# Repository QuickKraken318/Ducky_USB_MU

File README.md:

Original project: https://github.com/Seytonic/malduino

Not tested IRL yet

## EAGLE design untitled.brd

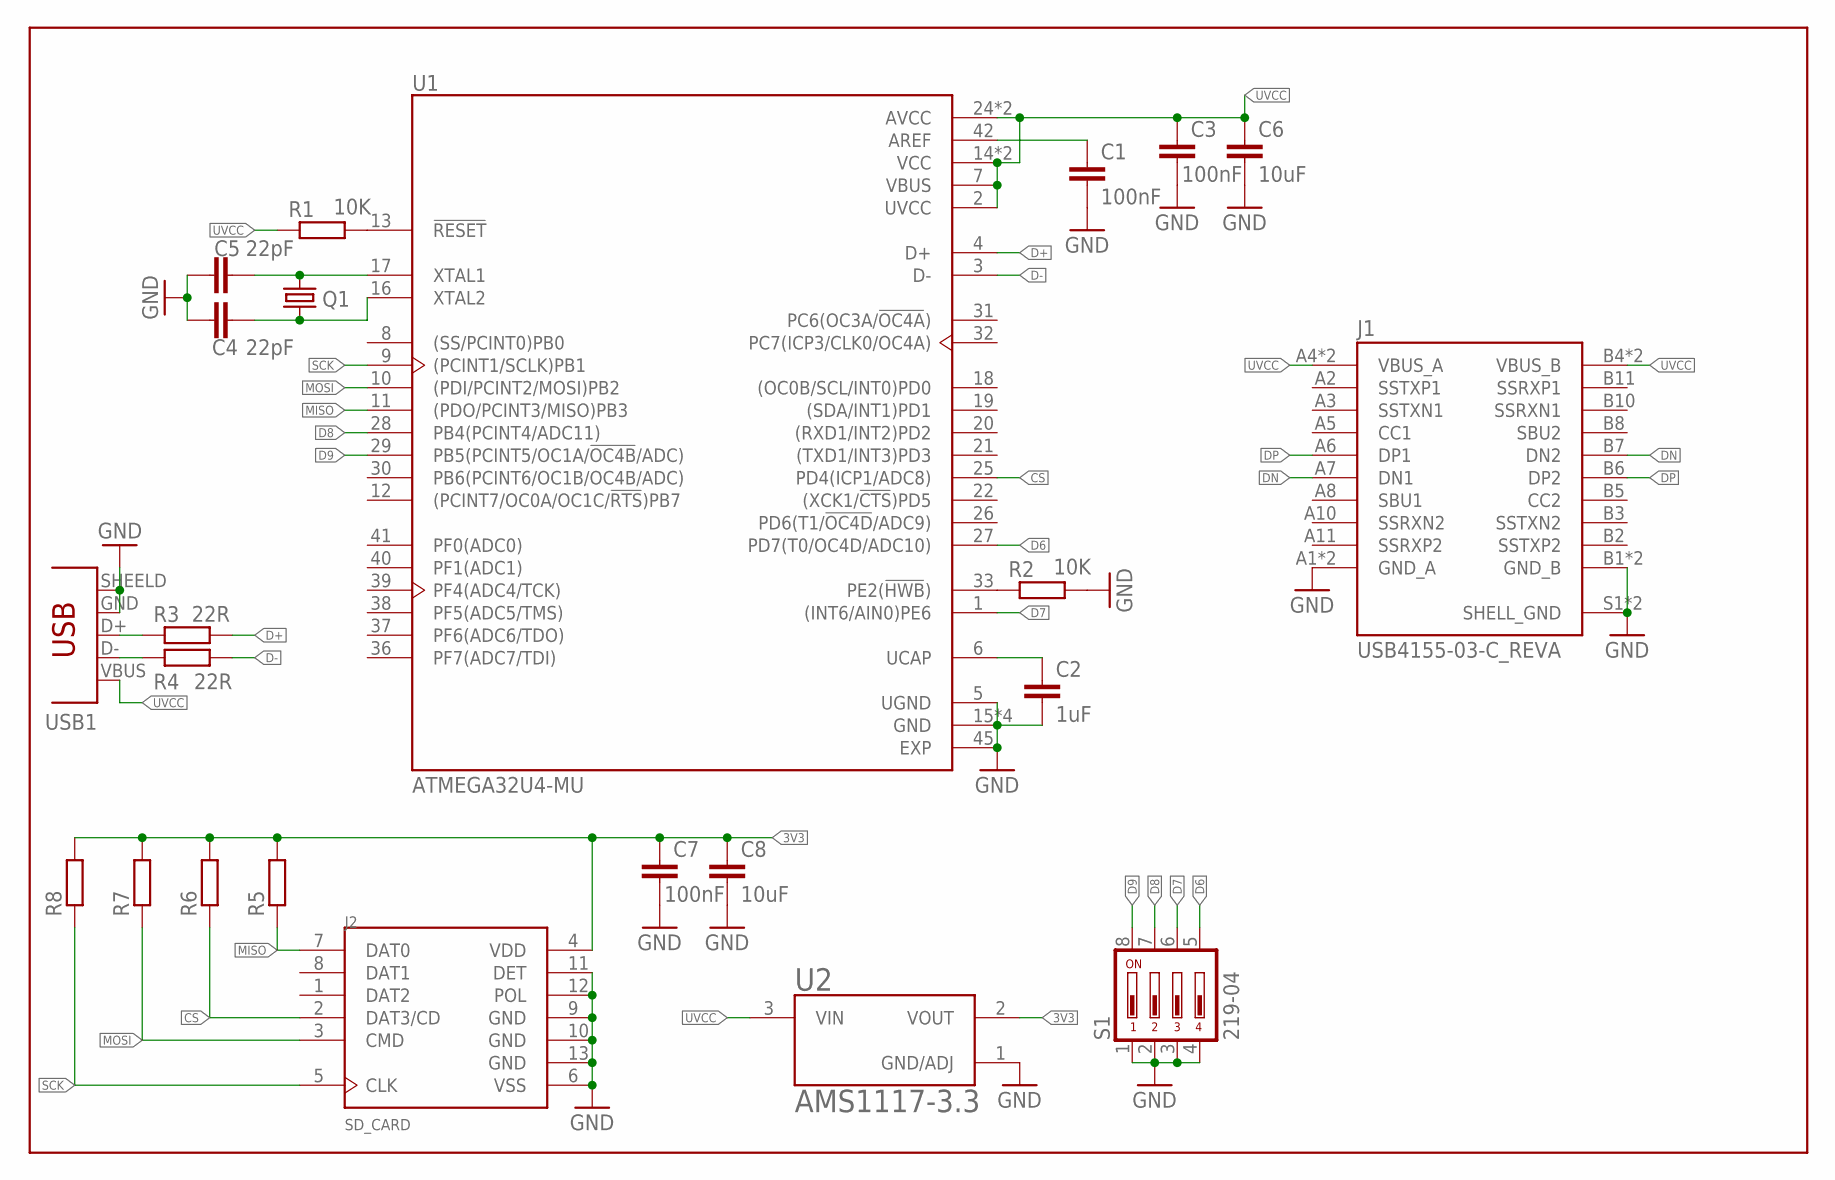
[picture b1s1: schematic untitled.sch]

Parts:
C1, C3, C7: 100nF; C0603
C2: 1uF; C0603
C4, C5: 22pF; C0603
C6, C8: 10uF; C0603
J1: USB4155-03-C_REVA; GCT_USB4155-03-C_REVA
J2: SD_CARD; MOLEX_0475710001
Q1: CRYSTALCTS406; CTS406
R1, R2: 10K; R0603
R3, R4: 22R; R0603
R5, R6, R7, R8: R-EU_R0603; R0603
S1: 219-04; CTS-219-04
U1: ATMEGA32U4-MU; QFN50P700X700X100-45N
U2: AMS1117-3.3; SOT229P700X180-4N
USB1: TYPE-A-MALE-SHILED; TYPE-A-MALE

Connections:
3V3: C7.1, C8.1, J2.4 (VDD), R5.2, R6.2, R7.2, R8.2, U2.2 (VOUT)
AREF: C1.1, U1.42 (AREF)
CS: J2.2 (DAT3/CD), R6.1, U1.25 (PD4(ICP1/ADC8))
D6: S1.5, U1.27 (PD7(T0/OC4D/ADC10))
D7: S1.6, U1.1 ((INT6/AIN0)PE6)
D8: S1.7, U1.28 (PB4(PCINT4/ADC11))
D9: S1.8, U1.29 (PB5(PCINT5/OC1A/!OC4B!/ADC))
D+: R3.2, U1.4 (D+)
D-: R4.2, U1.3 (D-)
DN: J1.A7 (DN1), J1.B7 (DN2), R4.1, USB1.D- (2)
DP: J1.A6 (DP1), J1.B6 (DP2), R3.1, USB1.D+ (3)
GND: C1.2, C2.2, C3.2, C4.1, C5.1, C6.2, C7.2, C8.2, J1.A1 (GND_A), J1.A12 (GND_A), J1.B1 (GND_B), J1.B12 (GND_B), J1.S1 (SHELL_GND), J1.S2 (SHELL_GND), J2.6 (VSS), J2.9 (GND), J2.10 (GND), J2.11 (DET), J2.12 (POL), J2.13 (GND), R2.2, S1.1, S1.2, S1.3, S1.4, U1.5 (UGND), U1.15 (GND), U1.23 (GND), U1.35 (GND), U1.43 (GND), U1.45 (EXP), U2.1 (GND/ADJ), USB1.GND (4), USB1.SHEELD (5)
MISO: J2.7 (DAT0), R5.1, U1.11 ((PDO/PCINT3/MISO)PB3)
MOSI: J2.3 (CMD), R7.1, U1.10 ((PDI/PCINT2/MOSI)PB2)
unnamed: R1.2, U1.13 (!RESET!)
unnamed: C2.1, U1.6 (UCAP)
unnamed: R2.1, U1.33 (PE2(!HWB!))
SCK: J2.5 (CLK), R8.1, U1.9 ((PCINT1/SCLK)PB1)
UVCC: C3.1, C6.1, J1.A4 (VBUS_A), J1.A9 (VBUS_A), J1.B4 (VBUS_B), J1.B9 (VBUS_B), R1.1, U1.2 (UVCC), U1.7 (VBUS), U1.14 (VCC), U1.24 (AVCC), U1.34 (VCC), U1.44 (AVCC), U2.3 (VIN), USB1.VBUS (1)
XTAL1: C5.2, Q1.3 (2), U1.17 (XTAL1)
XTAL2: C4.2, Q1.1, U1.16 (XTAL2)

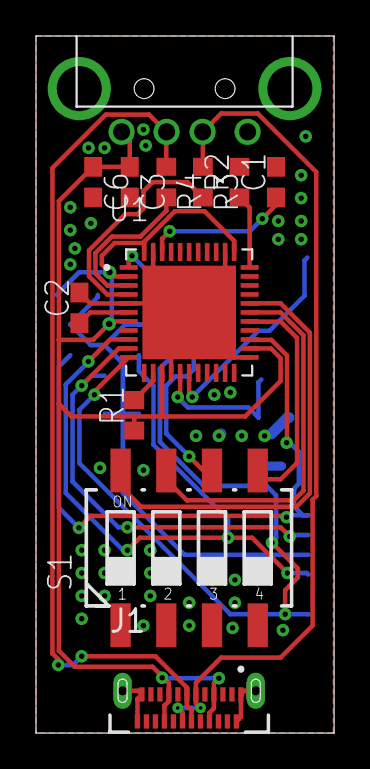
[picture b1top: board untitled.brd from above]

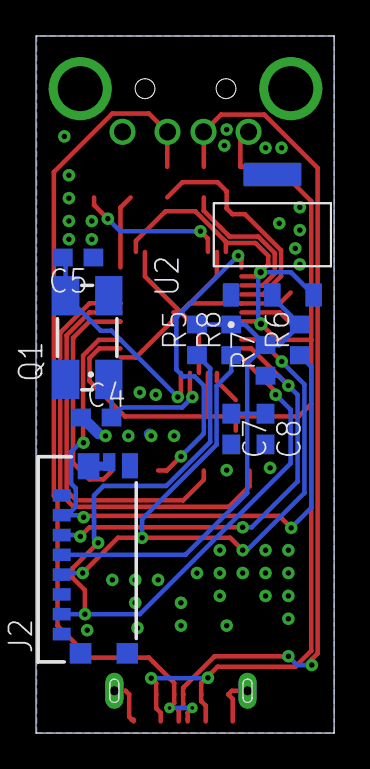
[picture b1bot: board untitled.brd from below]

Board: 2 copper layers, 16.6 x 38.7 mm, 23 parts (11 on the bottom side), 21 nets.
